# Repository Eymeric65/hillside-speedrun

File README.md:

# hillside-speedrun
Just a keyboard that I want to make ASAP.

This repo is my speedrun attempt to make a keyboard with my optimized library. Date start 26/05/2025 at 12h15

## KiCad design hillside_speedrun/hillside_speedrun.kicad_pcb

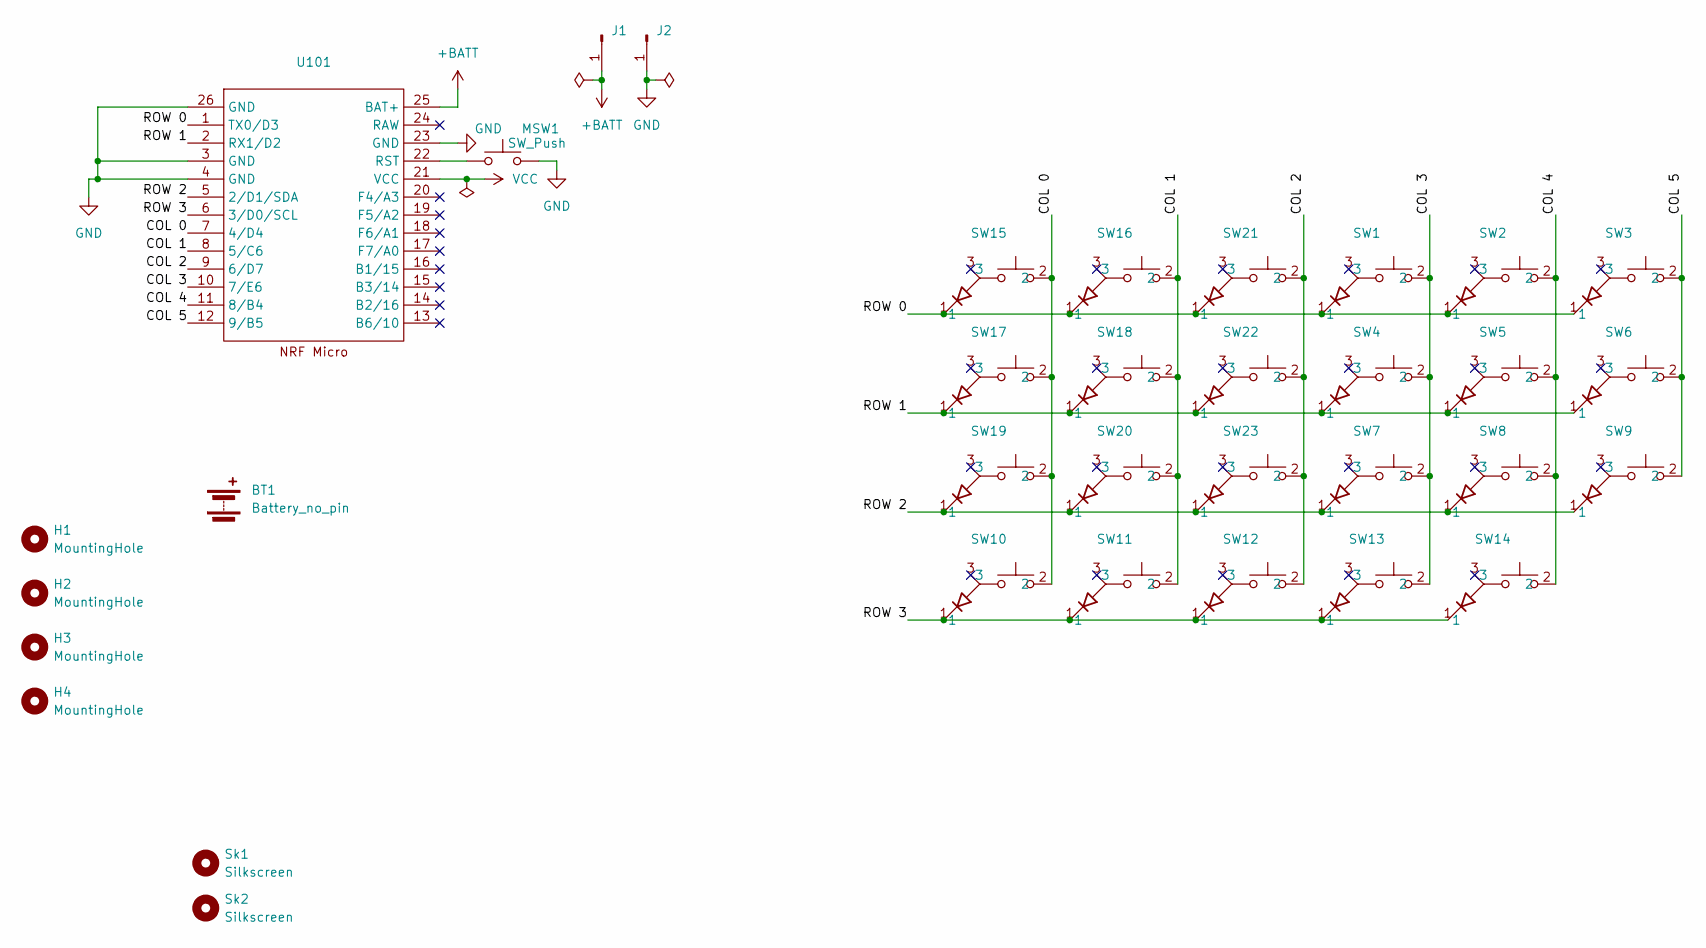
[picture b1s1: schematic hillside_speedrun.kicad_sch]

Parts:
BT1: Battery_no_pin; 503020 battery hole
H1, H2, H3, H4: MountingHole; MountingHole_2.2mm_M2_DIN965
J1, J2: Conn_01x01_Pin; Pin_D1.0mm_L10.0mm
MSW1: SW_Push; Reset_Switch
SW1, SW2, SW3, SW4, SW5, SW6, SW7, SW8, SW9, SW10, SW11, SW12, SW13, SW14, SW15, SW16, SW17, SW18, SW19, SW20, SW21, SW22, SW23: SW_UNIVERSAL_1.00u
Sk1, Sk2: Silkscreen; drawing
U101: ProMicro_DUAL_jumper

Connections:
+BATT: J1.1, U101.25 (BAT+)
/COL 0: SW10.2, SW15.2, SW17.2, SW19.2, U101.7 (4/D4)
/COL 1: SW11.2, SW16.2, SW18.2, SW20.2, U101.8 (5/C6)
/COL 2: SW12.2, SW21.2, SW22.2, SW23.2, U101.9 (6/D7)
/COL 3: SW1.2, SW4.2, SW7.2, SW13.2, U101.10 (7/E6)
/COL 4: SW2.2, SW5.2, SW8.2, SW14.2, U101.11 (8/B4)
/COL 5: SW3.2, SW6.2, SW9.2, U101.12 (9/B5)
/ROW 0: SW1.1, SW2.1, SW3.1, SW15.1, SW16.1, SW21.1, U101.1 (TX0/D3)
/ROW 1: SW4.1, SW5.1, SW6.1, SW17.1, SW18.1, SW22.1, U101.2 (RX1/D2)
/ROW 2: SW7.1, SW8.1, SW9.1, SW19.1, SW20.1, SW23.1, U101.5 (2/D1/SDA)
/ROW 3: SW10.1, SW11.1, SW12.1, SW13.1, SW14.1, U101.6 (3/D0/SCL)
GND: J2.1, MSW1.2, U101.3 (GND), U101.4 (GND), U101.23 (GND), U101.26 (GND)
unnamed: MSW1.1, U101.22 (RST)
VCC: U101.21 (VCC)

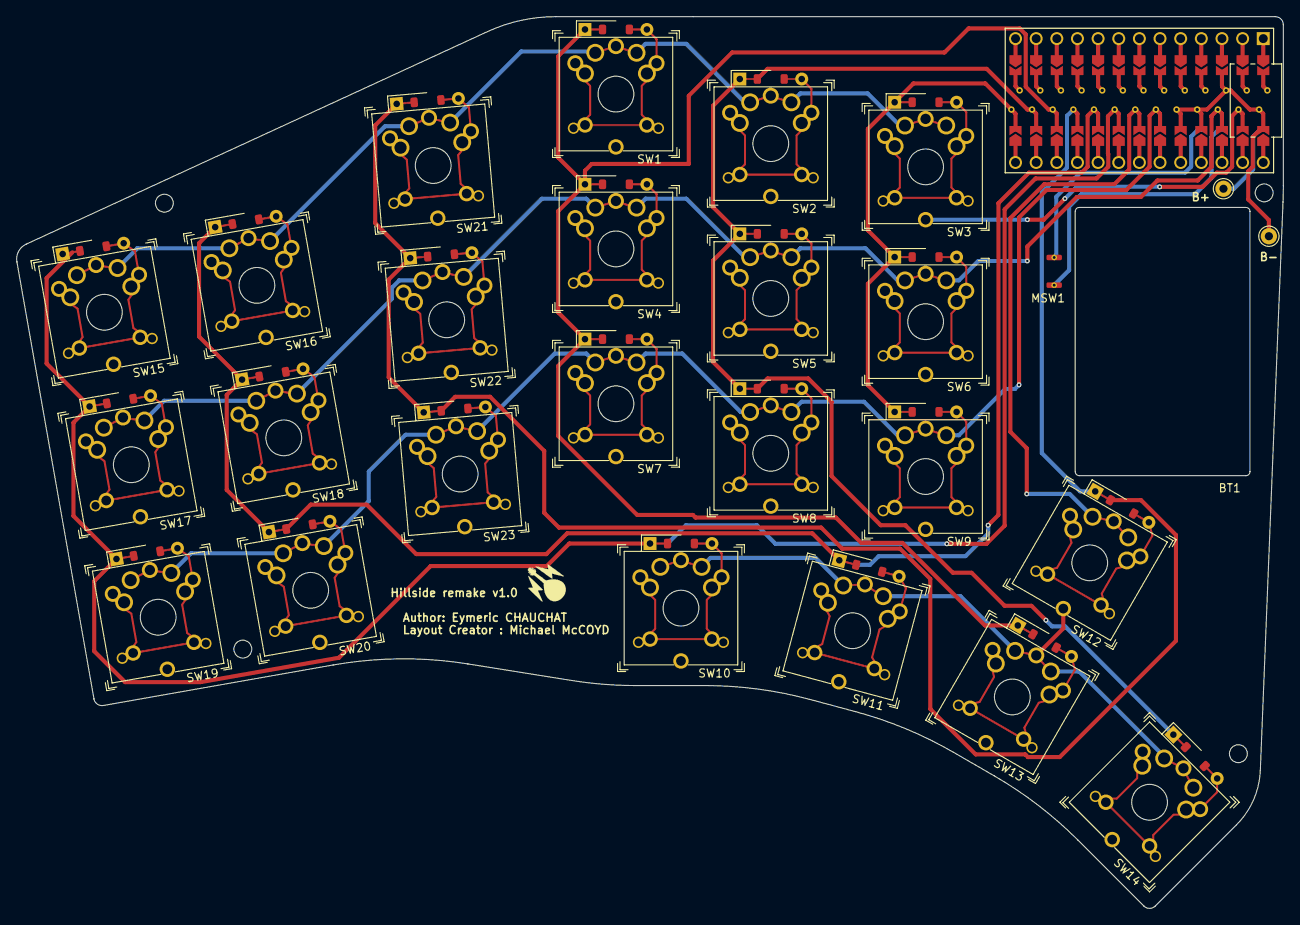
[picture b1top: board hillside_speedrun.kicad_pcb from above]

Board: 2 copper layers, 155.8 x 109.7 mm, 34 parts (1 on the bottom side), 13 nets.

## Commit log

2025-08-15 Deposit of the code and Kicad
